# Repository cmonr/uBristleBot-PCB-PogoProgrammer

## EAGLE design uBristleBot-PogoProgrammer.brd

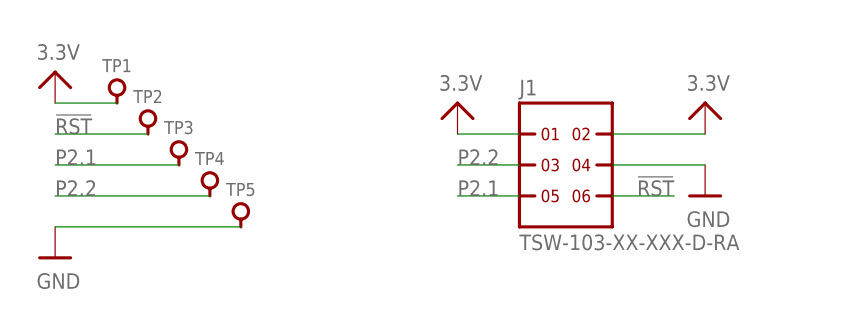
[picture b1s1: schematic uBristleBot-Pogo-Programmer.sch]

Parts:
J1: TSW-103-XX-XXX-D-RA
TP1, TP2, TP3, TP4, TP5: 0906-0

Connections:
3.3V: J1.1, J1.2, TP1.P$1
!RST: J1.6, TP2.P$1
GND: J1.4, TP5.P$1
P2.1: J1.5, TP3.P$1
P2.2: J1.3, TP4.P$1

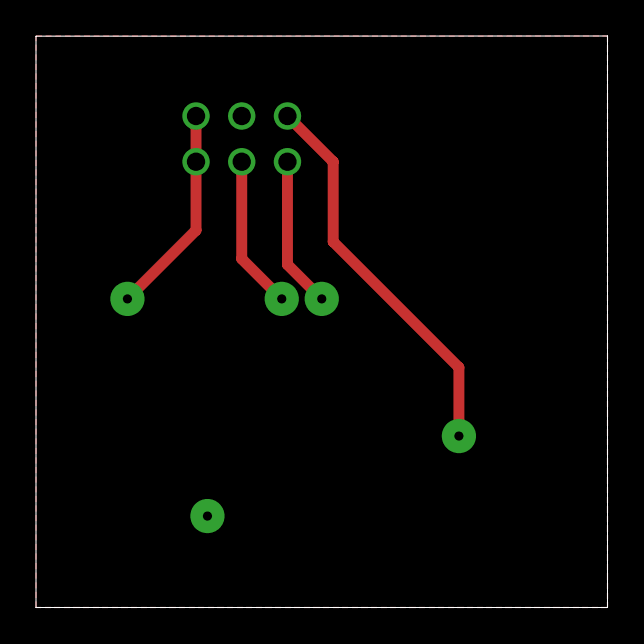
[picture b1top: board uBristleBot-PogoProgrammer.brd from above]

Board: 2 copper layers, 31.8 x 31.8 mm, 6 parts (1 on the bottom side), 5 nets.

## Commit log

2016-01-19 Initial commit of completed programmer
2016-01-19 Generated previews and added archive for easy ordering
2016-01-19 Did some minor file renaming
2016-01-19 Forgot to add the .zip for easy ordering

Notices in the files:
parts and their libraries:
microbuilder: This work is placed in the public domain, and may be freely used for commercial and non-commercial work with the following conditions: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
